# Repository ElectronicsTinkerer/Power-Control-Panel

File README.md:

# Custom Remote-Controlled Power Distribution Panel

The control panel provides control over eight individually switched outlets for managing the numerous gizmoes plugged in to your workbench. In addition, there is a master switch which overrides the rest of the panel for shutting down all outputs.

The device is constructed of two components. The first (pictured above) is the control panel. This contains a PCB that uses a shift register to parallel load the state of the input switches and send them over an ethernet-style cable to the second component, the relay board. The relay board is responsible for generating the clock and load signals used by the control panel. It also shifts in the data from the control panel and drives a bank of eight relays to control attached devices.

All the design files are included in this repo. For more background and pictures, checkout [my website](https://zrcn.org/power-control-panel.html).

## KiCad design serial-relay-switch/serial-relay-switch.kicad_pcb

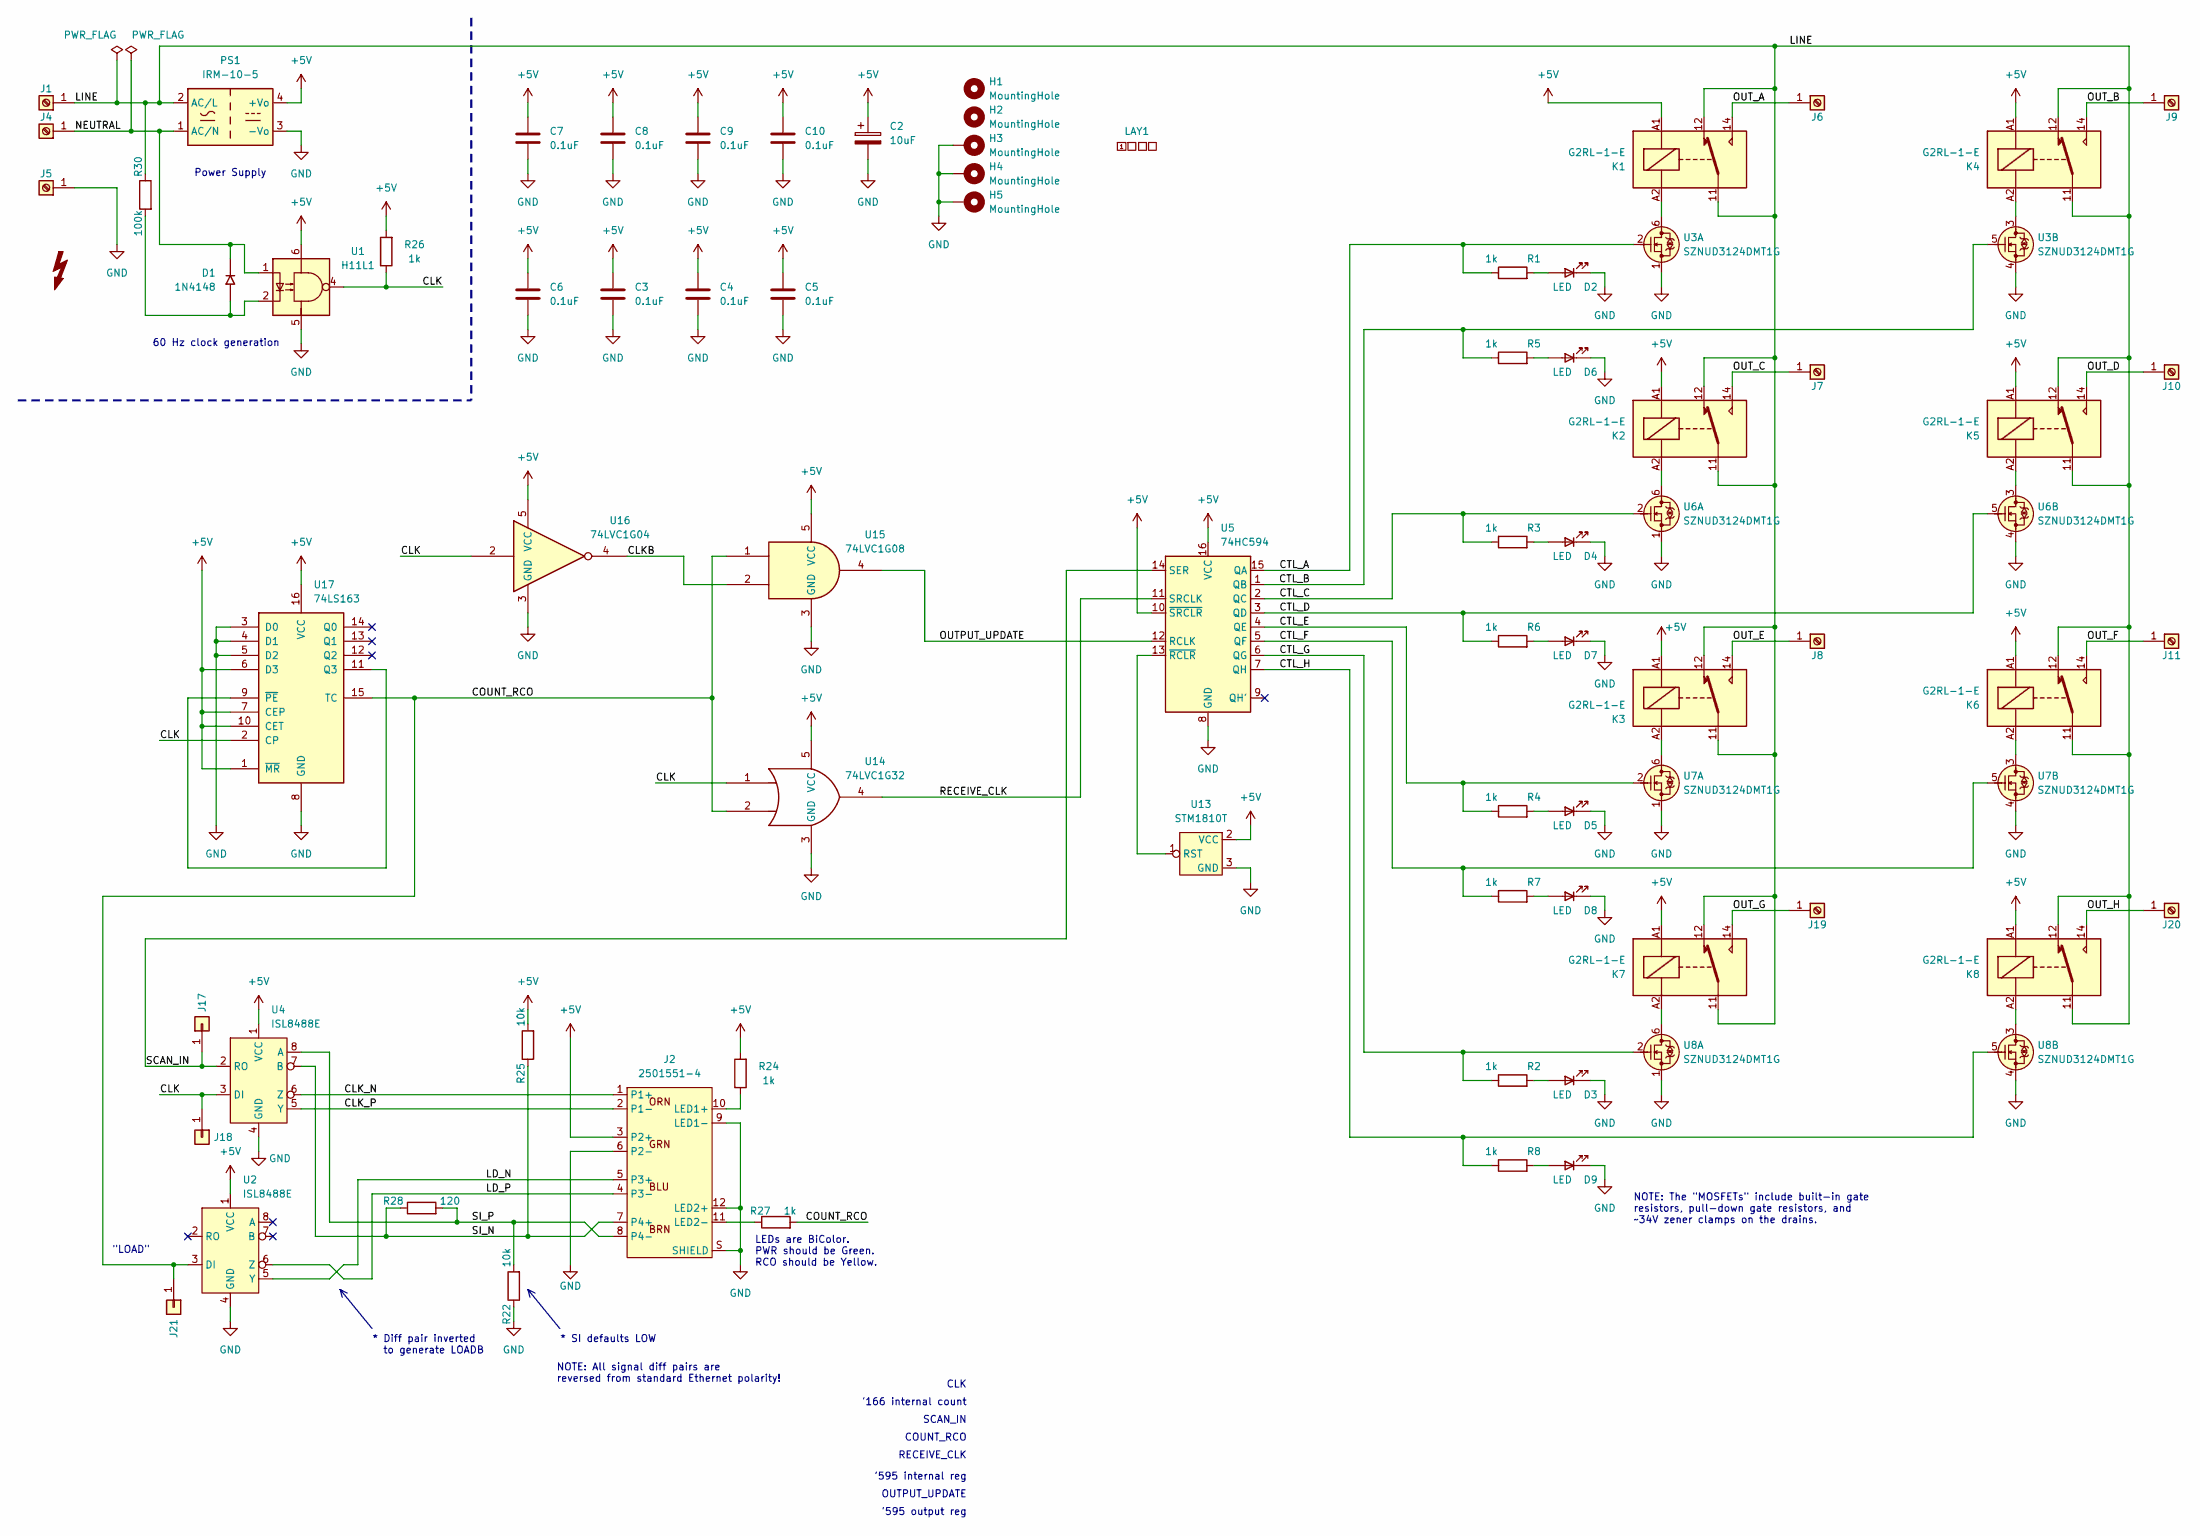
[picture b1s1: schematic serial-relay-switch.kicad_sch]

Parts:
C2: 10uF; C_Radial_D8.0mm_H7.0mm_P3.50mm
C3, C4, C5, C6, C7, C8, C9, C10: 0.1uF; C_0603_1608Metric
D1: 1N4148; D_SOD-123F
D2, D3, D4, D5, D6, D7, D8, D9: LED; LED_0603_1608Metric
H1, H2: MountingHole; MountingHole_3.2mm_M3_Keepout
H3, H5: MountingHole; MountingHole_3.2mm_M3_ISO14580_Pad_TopBottom
H4: MountingHole; MountingHole_3.2mm_M3_DIN965_Pad_TopBottom
J1, J4, J5, J6, J7, J8, J9, J10, J11, J19, J20: Screw_Terminal_01x01; ScrewTerminal_Keystone_8195
J2: 2501551-4; EthernetJack_TE_2501551-4
J17, J18, J21: Conn_01x01; Pin_D1.0mm
K1, K2, K3, K4, K5, K6, K7, K8: G2RL-1-E; Relay_SPDT_Omron_G2RL-1-E
LAY1: LayerMarker_2_3.81x2.54mm_TextH1mm_P1.27mm_BottomMirrored
PS1: IRM-10-5; Converter_ACDC_MeanWell_IRM-10-xx_THT
R1, R2, R3, R4, R5, R6, R7, R8, R24, R26, R27: 1k; R_0603_1608Metric
R22, R25: 10k; R_0603_1608Metric
R28: 120; R_0603_1608Metric
R30: 100k; R_Axial_DIN0414_L11.9mm_D4.5mm_P5.08mm_Vertical
U1: H11L1; DIP-6_W10.16mm_LongPads
U2, U4: ISL8488E; SOIC-8_3.9x4.9mm_P1.27mm
U3, U6, U7, U8: SZNUD3124DMT1G; SC-74-6_1.55x2.9mm_P0.95mm
U5: 74HC594; SOIC-16_3.9x9.9mm_P1.27mm
U13: STM1810T; SOT-23-3
U14: 74LVC1G32; SOT-23-5
U15: 74LVC1G08; SOT-23-5
U16: 74LVC1G04; SOT-23-5
U17: 74LS163; SOIC-16_3.9x9.9mm_P1.27mm

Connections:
+5V: C2.1, C3.1, C4.1, C5.1, C6.1, C7.1, C8.1, C9.1, C10.1, J2.3 (P2+), K1.A1, K2.A1, K3.A1, K4.A1, K5.A1, K6.A1, K7.A1, K8.A1, PS1.4 (+Vo), R24.2, R25.2, R26.2, U1.6, U2.1 (VCC), U4.1 (VCC), U5.10 (~SRCLR), U5.16 (VCC), U13.2 (VCC), U14.5 (VCC), U15.5 (VCC), U16.5 (VCC), U17.1 (~MR), U17.6 (D3), U17.7 (CEP), U17.10 (CET), U17.16 (VCC)
/CLK: J18.1 (Pin_1_1), R26.1, U1.4, U4.3 (DI), U14.1, U16.2, U17.2 (CP)
/CLKB: U15.2, U16.4
/CLK_N: J2.1 (P1+), U4.6 (Z)
/CLK_P: J2.2 (P1-), U4.5 (Y)
/COUNT_RCO: J21.1 (Pin_1_1), R27.2, U2.3 (DI), U14.2, U15.1, U17.15 (TC)
/CTL_A: R1.1, U3.2, U5.15 (QA)
/CTL_B: R5.1, U3.5, U5.1 (QB)
/CTL_C: R3.1, U5.2 (QC), U6.2
/CTL_D: R6.1, U5.3 (QD), U6.5
/CTL_E: R4.1, U5.4 (QE), U7.2
/CTL_F: R7.1, U5.5 (QF), U7.5
/CTL_G: R2.1, U5.6 (QG), U8.2
/CTL_H: R8.1, U5.7 (QH), U8.5
/LD_N: J2.5 (P3+), U2.5 (Y)
/LD_P: J2.4 (P3-), U2.6 (Z)
/LINE: J1.1 (Pin_1_1), K1.11, K1.12, K2.11, K2.12, K3.11, K3.12, K4.11, K4.12, K5.11, K5.12, K6.11, K6.12, K7.11, K7.12, K8.11, K8.12, PS1.2 (AC/L), R30.1
/NEUTRAL: D1.1 (K), J4.1 (Pin_1_1), PS1.1 (AC/N), U1.1
/OUTPUT_UPDATE: U5.12 (RCLK), U15.4
/OUT_A: J6.1 (Pin_1_1), K1.14
/OUT_B: J9.1 (Pin_1_1), K4.14
/OUT_C: J7.1 (Pin_1_1), K2.14
/OUT_D: J10.1 (Pin_1_1), K5.14
/OUT_E: J8.1 (Pin_1_1), K3.14
/OUT_F: J11.1 (Pin_1_1), K6.14
/OUT_G: J19.1 (Pin_1_1), K7.14
/OUT_H: J20.1 (Pin_1_1), K8.14
/RECEIVE_CLK: U5.11 (SRCLK), U14.4
/SCAN_IN: J17.1 (Pin_1_1), U4.2 (RO), U5.14 (SER)
/SI_N: J2.7 (P4+), R25.1, R28.1, U4.7 (B)
/SI_P: J2.8 (P4-), R22.2, R28.2, U4.8 (A)
GND: C2.2, C3.2, C4.2, C5.2, C6.2, C7.2, C8.2, C9.2, C10.2, D2.1 (K), D3.1 (K), D4.1 (K), D5.1 (K), D6.1 (K), D7.1 (K), D8.1 (K), D9.1 (K), H3.1 (1_1), H4.1 (1_1), H5.1 (1_1), J2.6 (P2-), J2.9 (LED1-), J2.12 (LED2+), J2.S (SHIELD), J5.1 (Pin_1_1), PS1.3 (-Vo), R22.1, U1.5, U2.4 (GND), U3.1, U3.4, U4.4 (GND), U5.8 (GND), U6.1, U6.4, U7.1, U7.4, U8.1, U8.4, U13.3 (GND), U14.3 (GND), U15.3 (GND), U16.3 (GND), U17.3 (D0), U17.4 (D1), U17.5 (D2), U17.8 (GND)
unnamed: D1.2 (A), R30.2, U1.2
unnamed: D2.2 (A), R1.2
unnamed: D3.2 (A), R2.2
unnamed: D4.2 (A), R3.2
unnamed: D5.2 (A), R4.2
unnamed: D6.2 (A), R5.2
unnamed: D7.2 (A), R6.2
unnamed: D8.2 (A), R7.2
unnamed: D9.2 (A), R8.2
unnamed: J2.10 (LED1+), R24.1
unnamed: J2.11 (LED2-), R27.1
unnamed: K1.A2, U3.6
unnamed: K2.A2, U6.6
unnamed: K3.A2, U7.6
unnamed: K4.A2, U3.3
unnamed: K5.A2, U6.3
unnamed: K6.A2, U7.3
unnamed: K7.A2, U8.6
unnamed: K8.A2, U8.3
unnamed: U5.13 (~RCLR), U13.1 (RST)
unnamed: U17.9 (~PE), U17.11 (Q3)

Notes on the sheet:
Power Supply
SCAN_IN
"LOAD"
'166 internal count
* Diff pair inverted to generate LOADB
* SI defaults LOW
60 Hz clock generation
NOTE: The "MOSFETs" include built-in gate resistors, pull-down gate resistors, and ~34V zener clamps on the drains.
CLK
COUNT_RCO
NOTE: All signal diff pairs are reversed from standard Ethernet polarity!
LEDs are BiColor. PWR should be Green. RCO should be Yellow.
'595 internal reg
'595 output reg
OUTPUT_UPDATE
RECEIVE_CLK

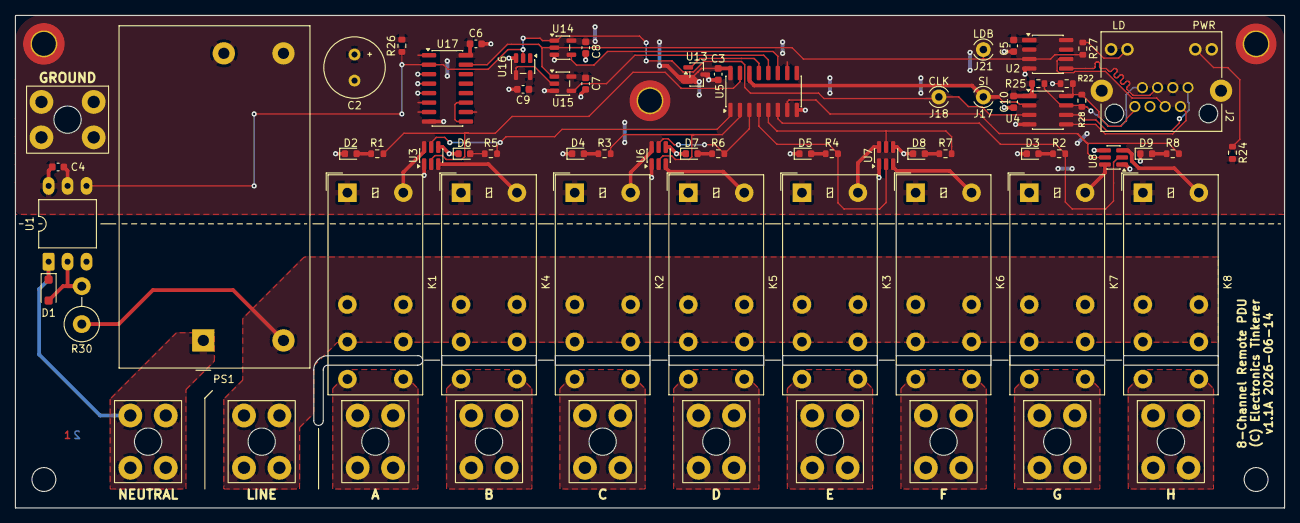
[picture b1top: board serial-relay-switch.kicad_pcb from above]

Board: 2 copper layers, 170.2 x 66.0 mm, 76 parts (0 on the bottom side), 53 nets.

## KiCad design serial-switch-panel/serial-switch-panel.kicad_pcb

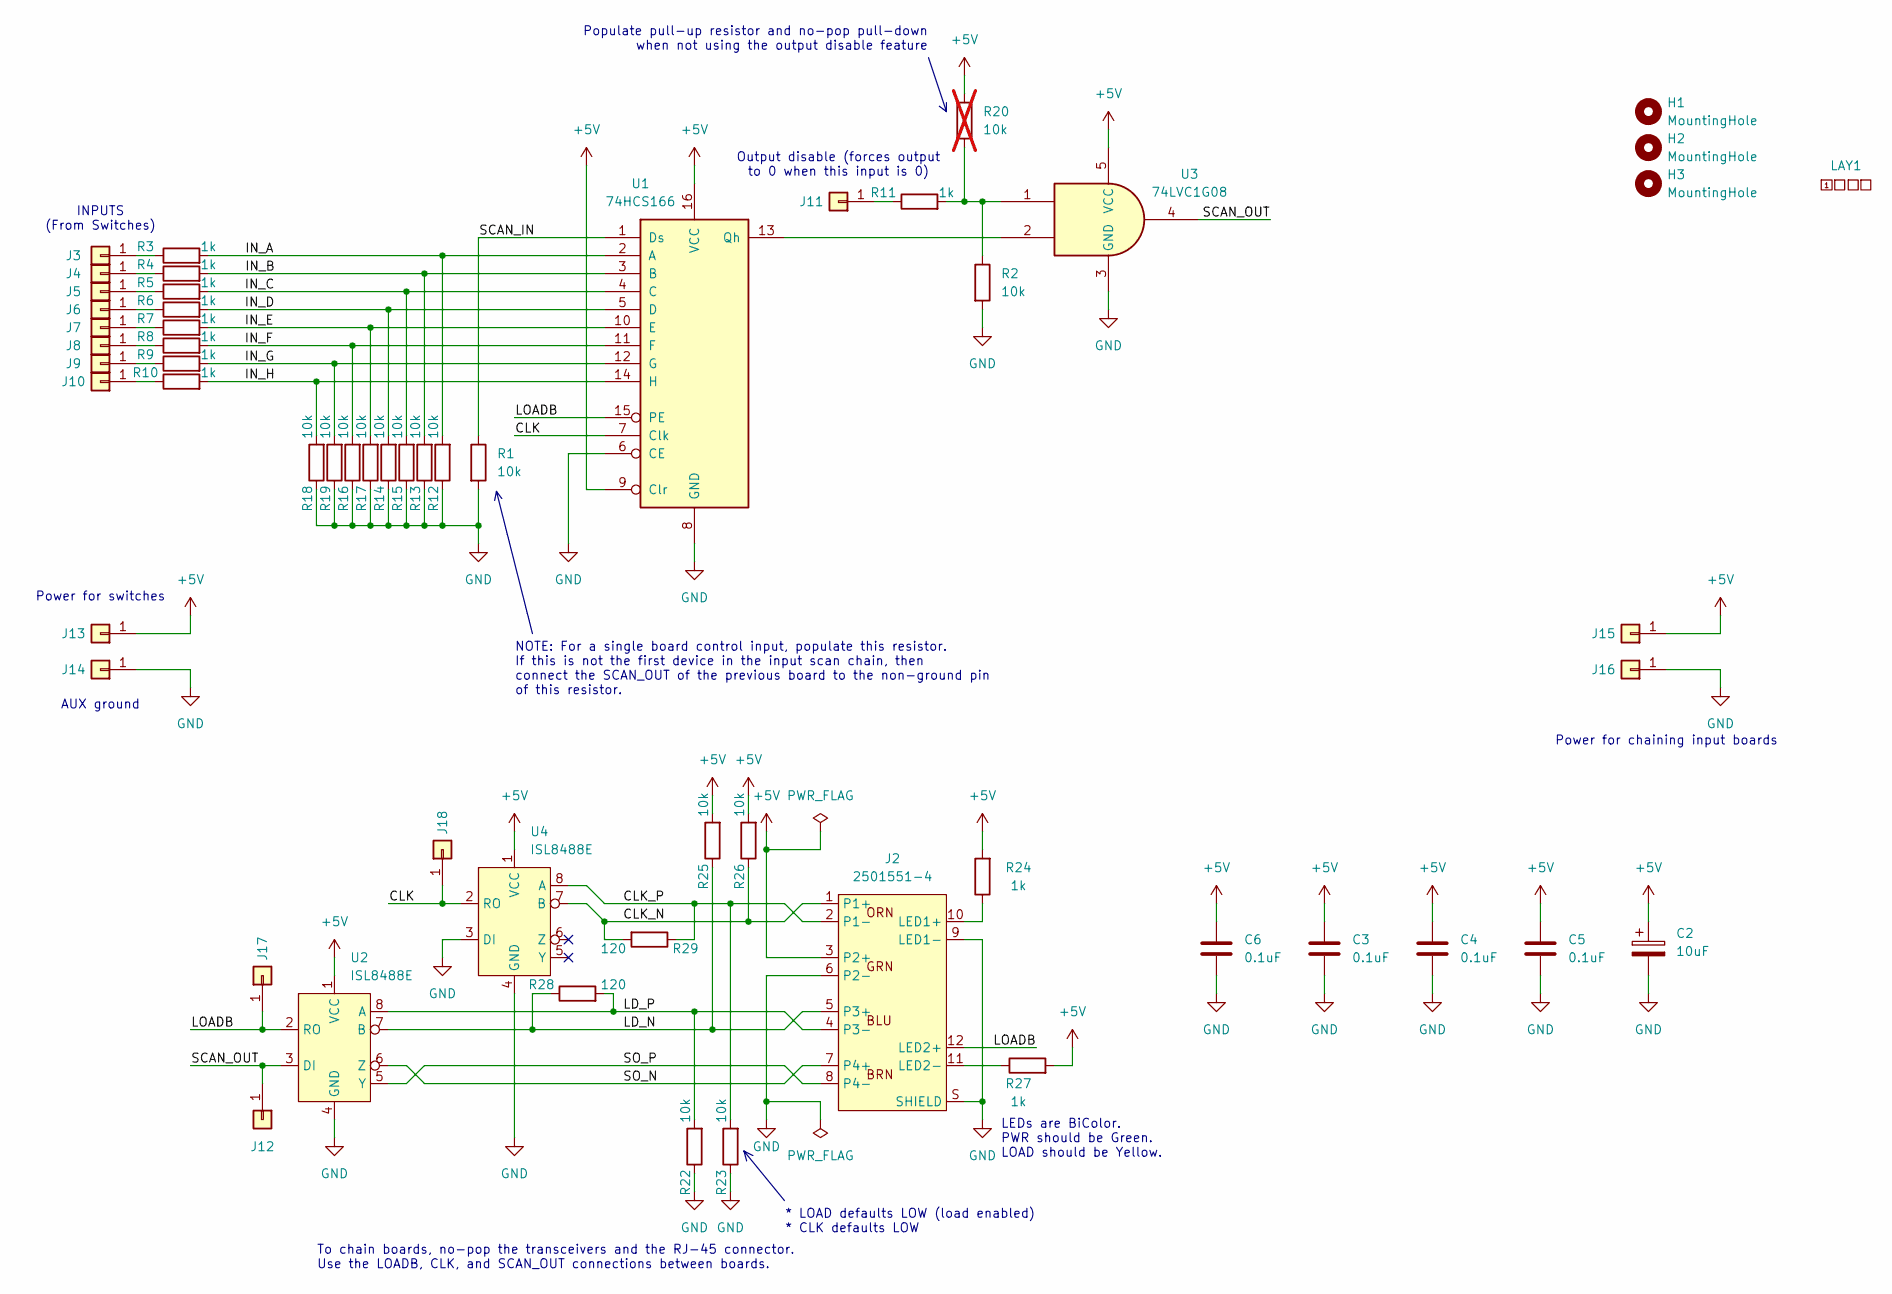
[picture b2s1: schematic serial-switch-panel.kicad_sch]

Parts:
C2: 10uF; C_1206_3216Metric
C3, C4, C5, C6: 0.1uF; C_0603_1608Metric
H1, H2, H3: MountingHole; MountingHole_3.2mm_M3
J2: 2501551-4
J3, J4, J5, J6, J7, J8, J9, J10, J11, J12, J13, J14, J15, J16, J17, J18: Conn_01x01; Pin_D1.0mm
LAY1: LayerMarker_2_3.81x2.54mm_TextH1mm_P1.27mm_BottomMirrored
R1: 10k; R_Axial_DIN0204_L3.6mm_D1.6mm_P2.54mm_Vertical
R2, R12, R13, R14, R15, R16, R17, R18, R19, R22, R23, R25, R26: 10k; R_0603_1608Metric
R3, R4, R5, R6, R7, R8, R9, R10, R11, R24, R27: 1k; R_0603_1608Metric
R20: 10k; R_0603_1608Metric; not fitted
R28, R29: 120; R_0603_1608Metric
U1: 74HCS166; SOIC-16_3.9x9.9mm_P1.27mm
U2, U4: ISL8488E; SOIC-8_3.9x4.9mm_P1.27mm
U3: 74LVC1G08; TSOP-5_1.65x3.05mm_P0.95mm

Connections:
+5V: C2.1, C3.1, C4.1, C5.1, C6.1, J2.3 (P2+), J13.1 (Pin_1_1), J15.1 (Pin_1_1), R20.1, R24.2, R25.2, R26.2, R27.2, U1.9 (Clr), U1.16 (VCC), U2.1 (VCC), U3.5 (VCC), U4.1 (VCC)
/CLK: J18.1 (Pin_1_1), U1.7 (Clk), U4.2 (RO)
/CLK_N: J2.1 (P1+), R26.1, R29.2, U4.7 (B)
/CLK_P: J2.2 (P1-), R23.2, R29.1, U4.8 (A)
/IN_A: R3.2, R12.2, U1.2 (A)
/IN_B: R4.2, R13.2, U1.3 (B)
/IN_C: R5.2, R15.2, U1.4 (C)
/IN_D: R6.2, R14.2, U1.5 (D)
/IN_E: R7.2, R17.2, U1.10 (E)
/IN_F: R8.2, R16.2, U1.11 (F)
/IN_G: R9.2, R19.2, U1.12 (G)
/IN_H: R10.2, R18.2, U1.14 (H)
/LD_N: J2.5 (P3+), R25.1, R28.1, U2.7 (B)
/LD_P: J2.4 (P3-), R22.2, R28.2, U2.8 (A)
/LOADB: J2.12 (LED2+), J17.1 (Pin_1_1), U1.15 (PE), U2.2 (RO)
/SCAN_IN: R1.1, U1.1 (Ds)
/SCAN_OUT: J12.1 (Pin_1_1), U2.3 (DI), U3.4
/SO_N: J2.7 (P4+), U2.6 (Z)
/SO_P: J2.8 (P4-), U2.5 (Y)
GND: C2.2, C3.2, C4.2, C5.2, C6.2, J2.6 (P2-), J2.9 (LED1-), J2.S (SHIELD), J14.1 (Pin_1_1), J16.1 (Pin_1_1), R1.2, R2.2, R12.1, R13.1, R14.1, R15.1, R16.1, R17.1, R18.1, R19.1, R22.1, R23.1, U1.6 (CE), U1.8 (GND), U2.4 (GND), U3.3 (GND), U4.3 (DI), U4.4 (GND)
unnamed: J2.10 (LED1+), R24.1
unnamed: J2.11 (LED2-), R27.1
unnamed: J3.1 (Pin_1_1), R3.1
unnamed: J4.1 (Pin_1_1), R4.1
unnamed: J5.1 (Pin_1_1), R5.1
unnamed: J6.1 (Pin_1_1), R6.1
unnamed: J7.1 (Pin_1_1), R7.1
unnamed: J8.1 (Pin_1_1), R8.1
unnamed: J9.1 (Pin_1_1), R9.1
unnamed: J10.1 (Pin_1_1), R10.1
unnamed: J11.1 (Pin_1_1), R11.1
unnamed: R2.1, R11.2, R20.2, U3.1
unnamed: U1.13 (Qh), U3.2

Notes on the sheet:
AUX ground
Power for chaining input boards
INPUTS (From Switches)
Power for switches
* LOAD defaults LOW (load enabled) * CLK defaults LOW
Populate pull-up resistor and no-pop pull-down when not using the output disable feature
NOTE: For a single board control input, populate this resistor. If this is not the first device in the input scan chain, then connect the SCAN_OUT of the previous board to the non-ground pin of this resistor.
To chain boards, no-pop the transceivers and the RJ-45 connector. Use the LOADB, CLK, and SCAN_OUT connections between boards.
LEDs are BiColor. PWR should be Green. LOAD should be Yellow.
Output disable (forces output to 0 when this input is 0)

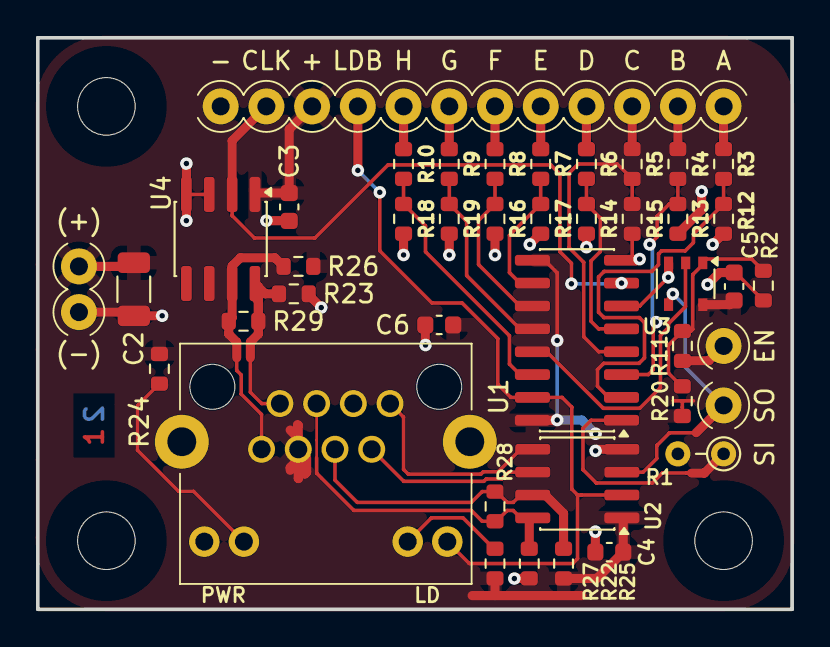
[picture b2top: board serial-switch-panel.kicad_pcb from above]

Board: 2 copper layers, 41.9 x 31.8 mm, 58 parts (0 on the bottom side), 33 nets.

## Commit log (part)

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2026-02-15 Create front-panel schematic
2026-02-15 Fix front-panel sch ERC
2026-02-15 Rough front-panel placement
2026-02-15 Final? front-panel placement
2026-02-15 [fp] Correct P4+/- swap in ethernet connector
2026-02-15 [fp] Complete board route
    Note: lots of DRC errors & warnings.
    - Warnings are silk overlaps - these are fine
    - Most errors are clearance violations on the shift register - waving these as still > 6mil
    - Remaining errors are thermal spokes on non-critical components & fill regions
2026-02-16 [rs] Start relay switch board
2026-02-16 [rs] Most of schematic complete
2026-02-16 [rs] Complete schematic
2026-02-16 [rs] Footprint assignment
2026-02-16 [rs] Mostly complete preliminary PCB placement
2026-02-16 [rs] New preliminary board layout
2026-02-17 [rs] Routing progress
2026-02-17 [rs] Routed, save for the pesky "Unrouted 1"
2026-02-17 [rs] Silk cleanup
2026-02-17 [rs] Ready for review
2026-02-28 [3d] Add 3D files for LED covers/mounts and Paddle Switches
2026-03-01 [3d] Document 3D directory contents
    Create README.MD
    Create 'rounded' version of paddle switch handle
    Add real picture of printed parts
2026-03-06 [fp] Add dimensions to mounting holes
2026-03-06 [fp][rs] Change hole footprints to no soldermask
2026-03-06 [fp] Add PCB dimensions to drawing layer
2026-03-06 [3d] Design Front panel sheet metal components
2026-03-07 [3d] Move Front Panel mount holes; export FP DXF
2026-03-07 [3d] Export FP rear DXF
2026-03-07 [3d] Add FP files to README
2026-03-07 [fp] Check/Finalize PCB
2026-03-07 [fp] Export gerbers v1.0A0
2026-03-08 [rs] Check/Finalize PCB; Export gerbers v1.0A0
2026-03-08 [3d] Create Outlet Panel
2026-03-08 [3d] Export outlet panel DXF
2026-03-09 [3d] Add insulator for relay PCB
2026-03-09 [rs] Add RJ-45 shield connection; Export v1.0A1 gerbers
2026-03-09 [fp] Add RJ-45 shield connection
2026-03-10 [docs] Add README about version numbers
2026-03-10 [fp] Change '166 to SOIC-16 footprint; Export v1.0A1 gerbers
    Wow, that one is tight (!)
2026-03-14 [3d] Re-export paddle switch bracket DXF
2026-05-18 [rs] Add PoR; Change to SC-74 coil driver package
2026-05-18 [rs] Route 97cfebe + export v1.0A2 gerbers
2026-05-18 [rs] used_designators backup file change
2026-05-18 [fp] Update schematic to kicad 10.0.2
2026-05-29 [rs] Update DRC rules; bump PCB to v1.0B
2026-05-29 [fp] Update DRC rules; bump PCB to v1.0B
2026-06-15 [rs] Add missing pullup on CLK; bump to v1.1A
